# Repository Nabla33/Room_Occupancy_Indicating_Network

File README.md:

# Room Occupancing Indicating Network

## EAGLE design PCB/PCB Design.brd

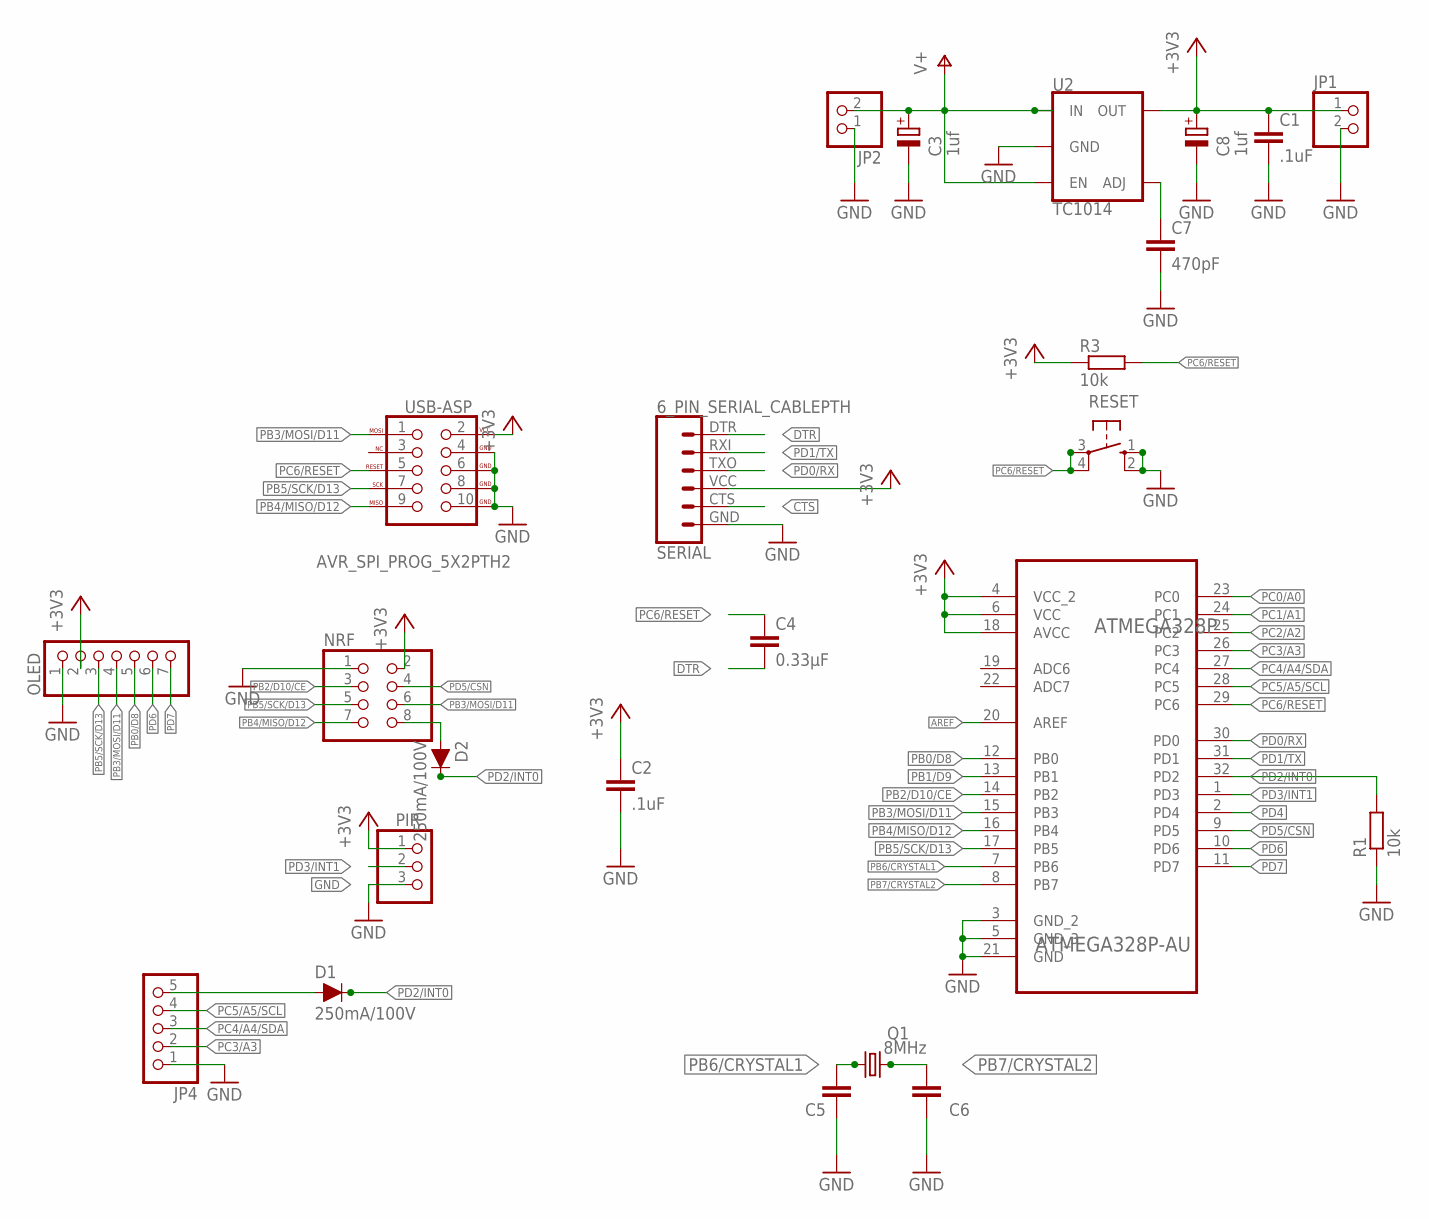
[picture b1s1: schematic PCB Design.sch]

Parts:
ATMEGA328P: ATMEGA328P-AU; QFP80P900X900X120-32N
C1, C2: .1uF; C0805K
C3, C8: 1uf; E2,5-5
C4: 0.33µF; C0805K
C5, C6: 22pF; C0805K
C7: 470pF; C0805K
D1, D2: 250mA/100V; SOD-323; MPN BNS33-11ZG-3M
JP1, JP2: PINHD-1X2; 1X02
JP4: PINHD-1X5; 1X05
NRF: PINHD-2X4; 2X04
OLED: PINHD-1X7; 1X07
PIR: PINHD-1X3; 1X03
Q1: 8MHz; HC49U70
R1, R3: 10k; M0805
RESET: 10-XX; B3F-10XX
SERIAL: 6_PIN_SERIAL_CABLEPTH; FTDI_BASIC
U2: TC1014; SOT23-5
USB-ASP: AVR_SPI_PROG_5X2PTH2; 2X5-SHROUDED

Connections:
8: D2.A, NRF.8
+3V3: ATMEGA328P.4 (VCC_2), ATMEGA328P.6 (VCC), ATMEGA328P.18 (AVCC), C1.1, C2.1, C8.+, JP1.1, NRF.2, OLED.2, PIR.1, R3.1, SERIAL.VCC (4), U2.5 (OUT), USB-ASP.2 (VCC)
AREF: ATMEGA328P.20 (AREF)
BYPASS: C7.1, U2.4 (ADJ)
CTS: SERIAL.CTS (5)
DTR: C4.2, SERIAL.DTR (1)
GND: ATMEGA328P.3 (GND_2), ATMEGA328P.5 (GND_3), ATMEGA328P.21 (GND), C1.2, C2.2, C3.-, C5.1, C6.1, C7.2, C8.-, JP1.2, JP2.1, JP4.1, NRF.1, OLED.1, PIR.3, R1.1, RESET.1 (S), RESET.2 (S1), SERIAL.GND (6), U2.2 (GND), USB-ASP.4 (GND), USB-ASP.6 (GND), USB-ASP.8 (GND), USB-ASP.10 (GND)
unnamed: D1.A, JP4.5
PB0/D8: ATMEGA328P.12 (PB0), OLED.5
PB1/D9: ATMEGA328P.13 (PB1)
PB2/D10/CE: ATMEGA328P.14 (PB2), NRF.3
PB3/MOSI/D11: ATMEGA328P.15 (PB3), NRF.6, OLED.4, USB-ASP.1 (MOSI)
PB4/MISO/D12: ATMEGA328P.16 (PB4), NRF.7, USB-ASP.9 (MISO)
PB5/SCK/D13: ATMEGA328P.17 (PB5), NRF.5, OLED.3, USB-ASP.7 (SCK)
PB6/CRYSTAL1: ATMEGA328P.7 (PB6), C5.2, Q1.1
PB7/CRYSTAL2: ATMEGA328P.8 (PB7), C6.2, Q1.2
PC0/A0: ATMEGA328P.23 (PC0)
PC1/A1: ATMEGA328P.24 (PC1)
PC2/A2: ATMEGA328P.25 (PC2)
PC3/A3: ATMEGA328P.26 (PC3), JP4.2
PC4/A4/SDA: ATMEGA328P.27 (PC4), JP4.3
PC5/A5/SCL: ATMEGA328P.28 (PC5), JP4.4
PC6/RESET: ATMEGA328P.29 (PC6), C4.1, R3.2, RESET.3, RESET.4 (P1), USB-ASP.5 (RESET)
PD0/RX: ATMEGA328P.30 (PD0), SERIAL.TXO (3)
PD1/TX: ATMEGA328P.31 (PD1), SERIAL.RXI (2)
PD2/INT0: ATMEGA328P.32 (PD2), D1.C, D2.C, R1.2
PD3/INT1: ATMEGA328P.1 (PD3), PIR.2
PD4: ATMEGA328P.2 (PD4)
PD5/CSN: ATMEGA328P.9 (PD5), NRF.4
PD6: ATMEGA328P.10 (PD6), OLED.6
PD7: ATMEGA328P.11 (PD7), OLED.7
V+: C3.+, JP2.2, U2.1 (IN), U2.3 (EN)

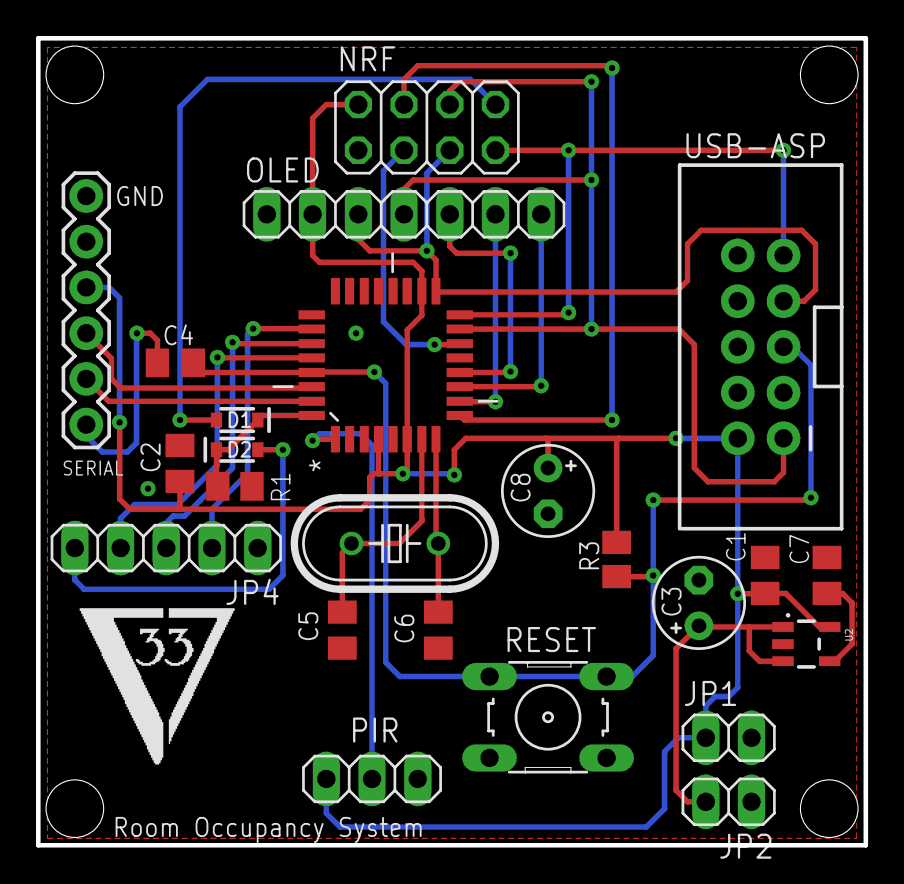
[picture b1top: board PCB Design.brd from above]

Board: 2 copper layers, 46.0 x 44.8 mm, 24 parts (0 on the bottom side), 25 nets.

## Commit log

2018-03-21 Basic Mesh Network with OLED setup done
2018-03-30 Shifted to Sloeber Eclipse IDE
2018-03-31 Created PCB folder and added designs
2018-03-31 Rearragned the board
2018-04-01 Added diode and rtc
2018-04-01 Added python scripts, updated code
2018-04-02 Generated Gerbers
2018-04-11 Updated Arduino code after HDD data loss
2018-04-11 Updated python scripts after HDD data loss
2018-04-11 Updated Python Scripts
2018-04-12 Added HTML and CSS
2018-04-12 GUI now works! Minor Ardunio Code fixes
2018-04-12 Added 3D printing files
2018-04-19 Added Documentation folder
2018-04-20 Working on poster and report
2018-04-20 Working on report
2018-04-20 Fixed text centering
2018-04-21 Added paper
2018-04-21 Updated Project Report and Paper
2018-05-16 Fixed Merge Now i think
2018-05-17 Wake up
2018-05-17 Finished project report and technical paper for final demo
2018-06-07 After final Demo
2018-06-11 Before internship backup

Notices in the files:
parts and their libraries:
SparkFun-Connectors: Licensing: Creative Commons ShareAlike 4.0 International - https://creativecommons.org/licenses/by-sa/4.0
